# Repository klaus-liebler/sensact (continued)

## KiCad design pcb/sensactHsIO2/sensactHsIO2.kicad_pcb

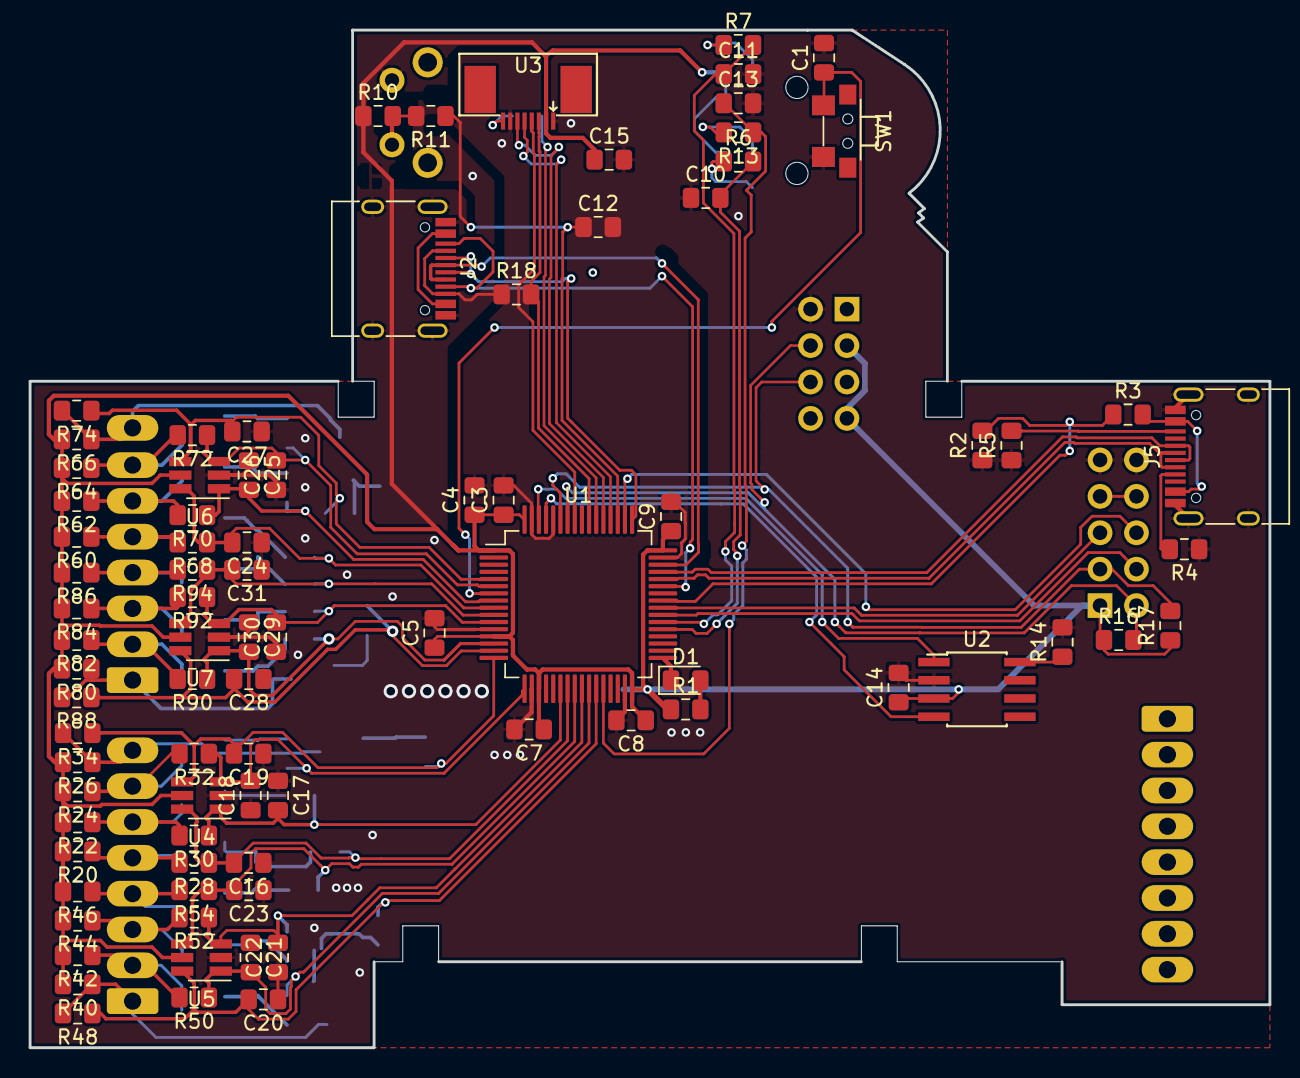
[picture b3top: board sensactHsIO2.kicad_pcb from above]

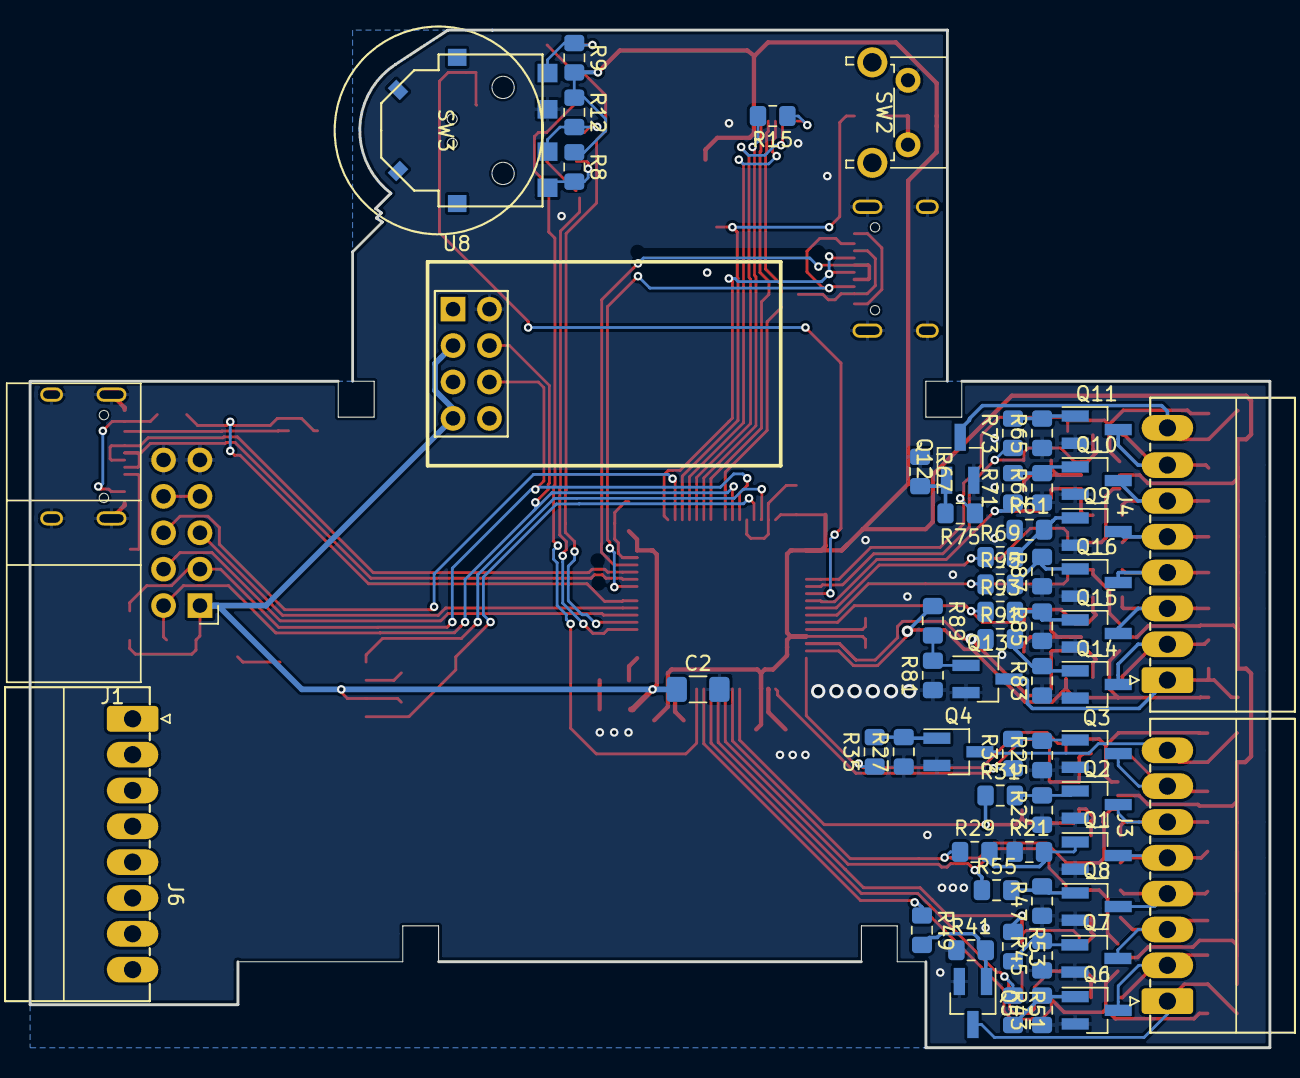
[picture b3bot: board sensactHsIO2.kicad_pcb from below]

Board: 2 copper layers, 86.5 x 71.0 mm, 146 parts (60 on the bottom side), 89 nets.

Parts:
C1, C3, C4, C5, C7, C8, C9, C10, C11, C12, C13, C14, C15, C16, C17, C18, C19, C20, C21, C22, C23, C24, C25, C26, C27, C28, C29, C30, C31: u1; C_0805_2012Metric_Pad1.15x1.40mm_HandSolder
C2: 4u7; C_1206_3216Metric_Pad1.42x1.75mm_HandSolder
D1: LED; LED_0805_2012Metric_Pad1.15x1.40mm_HandSolder
J1: SensactBus; IDC-Header_2x05_P2.54mm_Horizontal
J2, J5: USB_C_Receptacle_USB2.0; USB_C_Receptacle_HRO_TYPE-C-31-M-12
J3, J4, J6: Conn_01x08; PhoenixContact_MC_0,5_8-G-2.5_1x08_P2.50mm_Horizontal
Q1, Q2, Q3, Q4, Q5, Q6, Q7, Q8, Q9, Q10, Q11, Q12, Q13, Q14, Q15, Q16: Q_NMOS_GSD; SOT-23_Handsoldering
R1: K1; R_0805_2012Metric_Pad1.15x1.40mm_HandSolder
R2: 3k3; R_0805_2012Metric_Pad1.15x1.40mm_HandSolder
R3: 2k2; R_0805_2012Metric_Pad1.15x1.40mm_HandSolder
R4, R5: 5k1; R_0805_2012Metric_Pad1.15x1.40mm_HandSolder
R6, R7, R8, R9, R10, R11, R12, R13, R16, R17, R29, R31, R33, R35, R49, R51, R53, R55, R69, R71, R73, R75, R89, R91, R93, R95: 1k; R_0805_2012Metric_Pad1.15x1.40mm_HandSolder
R14, R20, R21, R22, R23, R24, R25, R26, R27, R28, R30, R32, R34, R40, R41, R42, R43, R44, R45, R46, R47, R48, R50, R52, R54, R60, R61, R62, R63, R64, R65, R66, R67, R68, R70, R72, R74, R80, R81, R82, R83, R84, R85, R86, R87, R88, R90, R92, R94: 10k; R_0805_2012Metric_Pad1.15x1.40mm_HandSolder
R15: 10R; R_0805_2012Metric_Pad1.15x1.40mm_HandSolder
R18: 22R; R_0805_2012Metric_Pad1.15x1.40mm_HandSolder
SW1: Reset; SW_SPST_2x4x3,5
SW2: SW_Push; SW_Tactile_SPST_Angled_PTS645Vx83-2LFS
SW3: Mitsumi_SIQ-02FVS3
U1: STM32F103R8Tx; LQFP-64_10x10mm_P0.5mm_handsolder
U2: SN65HVD230; SOIC-8_3.9x4.9mm_Pitch1.27mm_handsolder
U3: FP-096H09A; FPC_TOP_1x08-1MP_P0.50mm_Horizontal
U4, U5, U6, U7: SRV05-4; SOT-23-6_Handsoldering
U8: ESP-01v090; ESP-01

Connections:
+3V3: C2.1, C3.1, C4.1, C5.1, C7.1, C8.1, C9.1, C14.1, C15.1, J1.1, R1.1, R8.1, R9.2, R10.1, R12.1, R16.1, R17.1, R20.2, R22.2, R24.2, R26.2, R40.2, R42.2, R44.2, R46.2, R60.2, R62.2, R64.2, R66.2, R80.2, R82.2, R84.2, R86.2, U1.1, U1.13, U1.19, U1.32, U1.48, U1.64, U2.3, U3.2, U4.5, U5.5, U6.5, U7.5, U8.3, U8.7
+24V: J1.7, J1.8
/INT0: J1.4, U1.39
/INT1: J1.5, U1.40
/INT2: J1.6, U1.50
/NRST: C1.1, SW1.1, U1.7
/RX: J2.A8, J2.B8, U1.43
/SWCLK: J2.A7, J2.B7, U1.49
/SWDIO: J2.A6, J2.B6, U1.46
/USB+: J5.A6, J5.B6, U1.45
/USB-: J5.A7, J5.B7, U1.44
/io4_0/OUT0: J3.1, Q5.3, R40.1, R48.2
/io4_0/OUT1: J3.2, Q6.3, R42.1, R50.2
/io4_0/OUT2: J3.3, Q7.3, R44.1, R52.2
/io4_0/OUT3: J3.4, Q8.3, R46.1, R54.2
/io4_1/OUT0: J3.5, Q1.3, R20.1, R28.2
/io4_1/OUT1: J3.6, Q2.3, R22.1, R30.2
/io4_1/OUT2: J3.7, Q3.3, R24.1, R32.2
/io4_1/OUT3: J3.8, Q4.3, R26.1, R34.2
/io4_2/OUT0: J4.1, Q13.3, R80.1, R88.2
/io4_2/OUT1: J4.2, Q14.3, R82.1, R90.2
/io4_2/OUT2: J4.3, Q15.3, R84.1, R92.2
/io4_2/OUT3: J4.4, Q16.3, R86.1, R94.2
/io4_3/OUT0: J4.5, Q9.3, R60.1, R68.2
/io4_3/OUT1: J4.6, Q10.3, R62.1, R70.2
/io4_3/OUT2: J4.7, Q11.3, R64.1, R72.2
/io4_3/OUT3: J4.8, Q12.3, R66.1, R74.2
CAN_RX: U1.61, U2.4
CAN_TX: U1.62, U2.1
DAC0: J6.1, U1.20
DAC1: J6.2, U1.21
GND: C1.2, C2.2, C3.2, C4.2, C5.2, C7.2, C8.2, C9.2, C10.1, C11.2, C12.2, C13.2, C14.2, C15.2, C16.1, C17.1, C18.1, C19.1, C20.1, C21.1, C22.1, C23.1, C24.1, C25.1, C26.1, C27.1, C28.1, C29.1, C30.1, C31.1, J1.9, J1.10, J2.A1, J2.A12, J2.B1, J2.B12, J2.S1, J5.A1, J5.A12, J5.B1, J5.B12, J5.S1, Q1.2, Q2.2, Q3.2, Q4.2, Q5.2, Q6.2, Q7.2, Q8.2, Q9.2, Q10.2, Q11.2, Q12.2, Q13.2, Q14.2, Q15.2, Q16.2, R2.1, R4.1, R5.1, R14.2, R21.1, R23.1, R25.1, R27.1, R41.1, R43.1, R45.1, R47.1, R61.1, R63.1, R65.1, R67.1, R81.1, R83.1, R85.1, R87.1, SW1.2, SW2.1, SW3.C, U1.12, U1.18, U1.31, U1.47, U1.60, U1.63, U2.2, U3.1, U3.7, U4.2, U5.2, U6.2, U7.2, U8.2
I00: C20.2, R48.1, R49.1, U1.27, U5.6
I01: C21.2, R50.1, R51.1, U1.26, U5.1
I02: C22.2, R52.1, R53.1, U1.25, U5.3
I03: C23.2, R54.1, R55.1, U1.24, U5.4
I04: C16.2, R28.1, R29.1, U1.23, U4.6
I05: C17.2, R30.1, R31.1, U1.22, U4.1
I06: C18.2, R32.1, R33.1, U1.17, U4.3
I07: C19.2, R34.1, R35.1, U1.16, U4.4
I08: C28.2, R88.1, R89.1, U1.15, U7.6
I09: C29.2, R90.1, R91.1, U1.14, U7.1
I10: C30.2, R92.1, R93.1, U1.11, U7.3
I11: C31.2, R94.1, R95.1, U1.10, U7.4
I12: C24.2, R68.1, R69.1, U1.9, U6.6
I13: C25.2, R70.1, R71.1, U1.8, U6.1
I14: C26.2, R72.1, R73.1, U1.6, U6.3
I15: C27.2, R74.1, R75.1, U1.5, U6.4
LCD_BL: R15.2, U1.54
LCD_CLK: R18.2, U1.55, U3.3
LCD_MOSI: U1.57, U3.4
LCD_RS: U1.52, U3.5
LCD_RST: U1.53, U3.6
LED: D1.1, U1.33
unnamed: D1.2, R1.2
unnamed: J2.A4, J2.A9, J2.B4, J2.B9
unnamed: J5.A4, J5.A9, J5.B4, J5.B9, R3.2
unnamed: J5.A5, R4.2
unnamed: J5.B5, R5.2
unnamed: Q1.1, R21.2, R29.2
unnamed: Q2.1, R23.2, R31.2
unnamed: Q3.1, R25.2, R33.2
unnamed: Q4.1, R27.2, R35.2
unnamed: Q5.1, R41.2, R49.2
unnamed: Q6.1, R43.2, R51.2
unnamed: Q7.1, R45.2, R53.2
unnamed: Q8.1, R47.2, R55.2
unnamed: Q9.1, R61.2, R69.2
unnamed: Q10.1, R63.2, R71.2
unnamed: Q11.1, R65.2, R73.2
unnamed: Q12.1, R67.2, R75.2
unnamed: Q13.1, R81.2, R89.2
unnamed: Q14.1, R83.2, R91.2
unnamed: Q15.1, R85.2, R93.2
unnamed: Q16.1, R87.2, R95.2
unnamed: R6.1, R8.2, SW3.A
unnamed: R7.1, R9.1, SW3.B
unnamed: R10.2, R11.2, SW2.2
unnamed: R12.2, R13.2, SW3.S
unnamed: R14.1, U2.8
unnamed: R15.1, U3.8
ROTA: C10.2, R6.2, U1.37
ROTB: C11.1, R7.2, U1.38
ROTS: C13.1, R13.1, U1.28
S: C12.1, R11.1, U1.51
SCL1: J1.2, R16.2, U1.58, U8.4
SDA1: J1.3, R17.2, U1.59, U8.6
SWO: J2.A5, J2.B5, R18.1
VBUS: R2.2, R3.1, U1.41

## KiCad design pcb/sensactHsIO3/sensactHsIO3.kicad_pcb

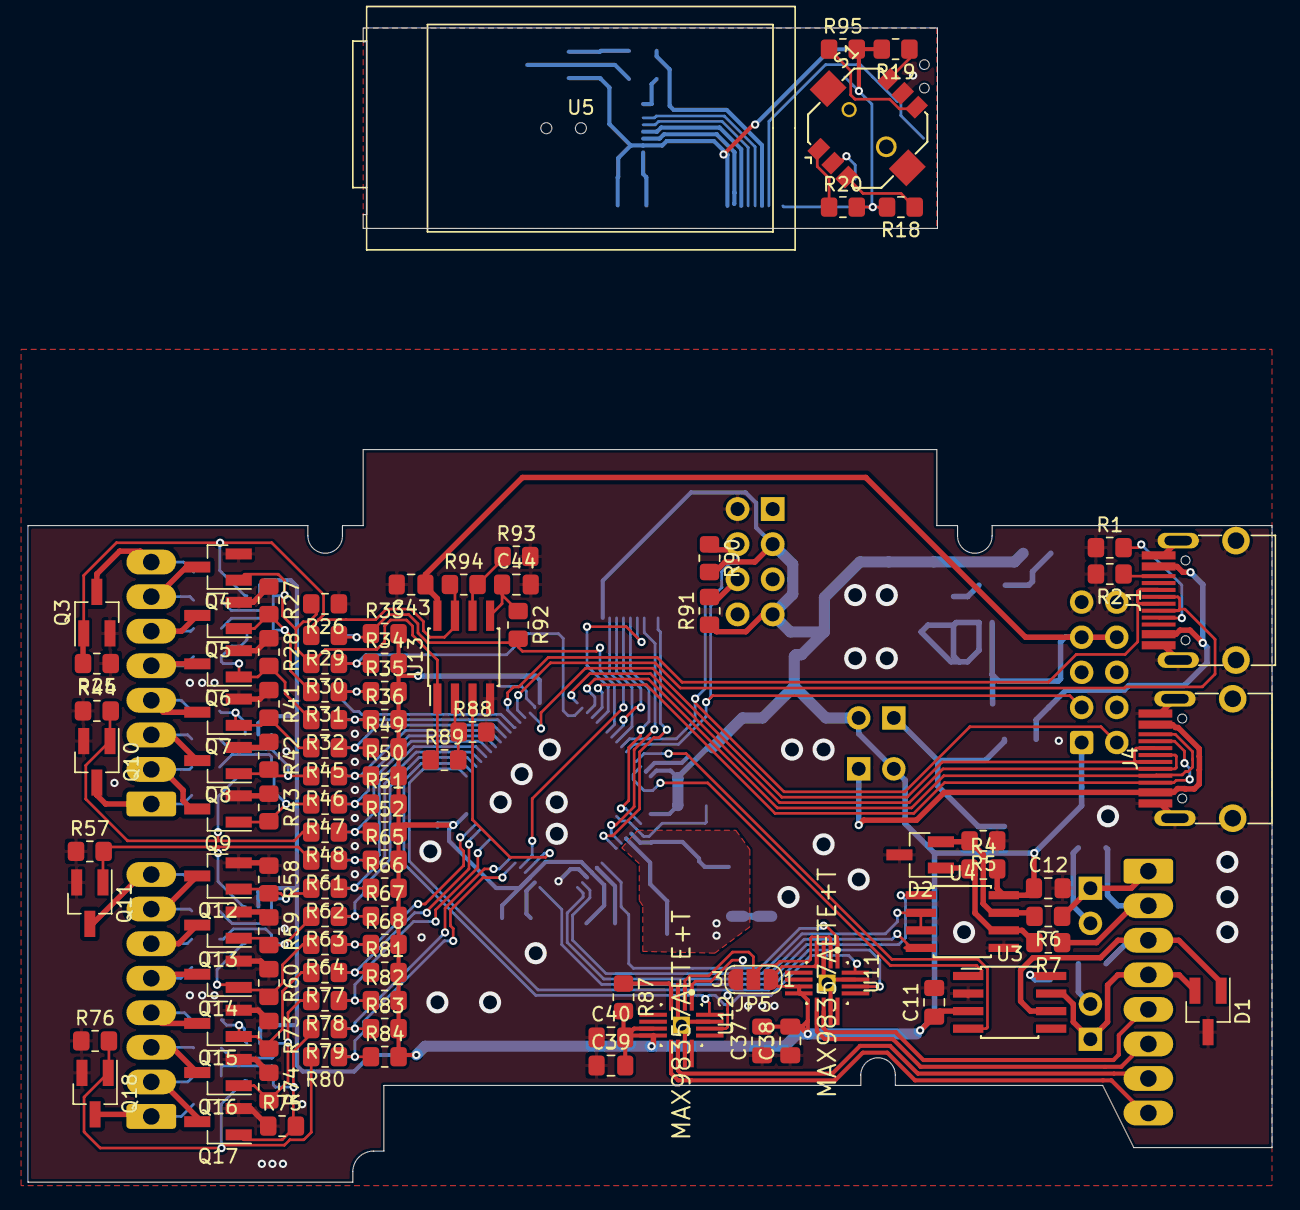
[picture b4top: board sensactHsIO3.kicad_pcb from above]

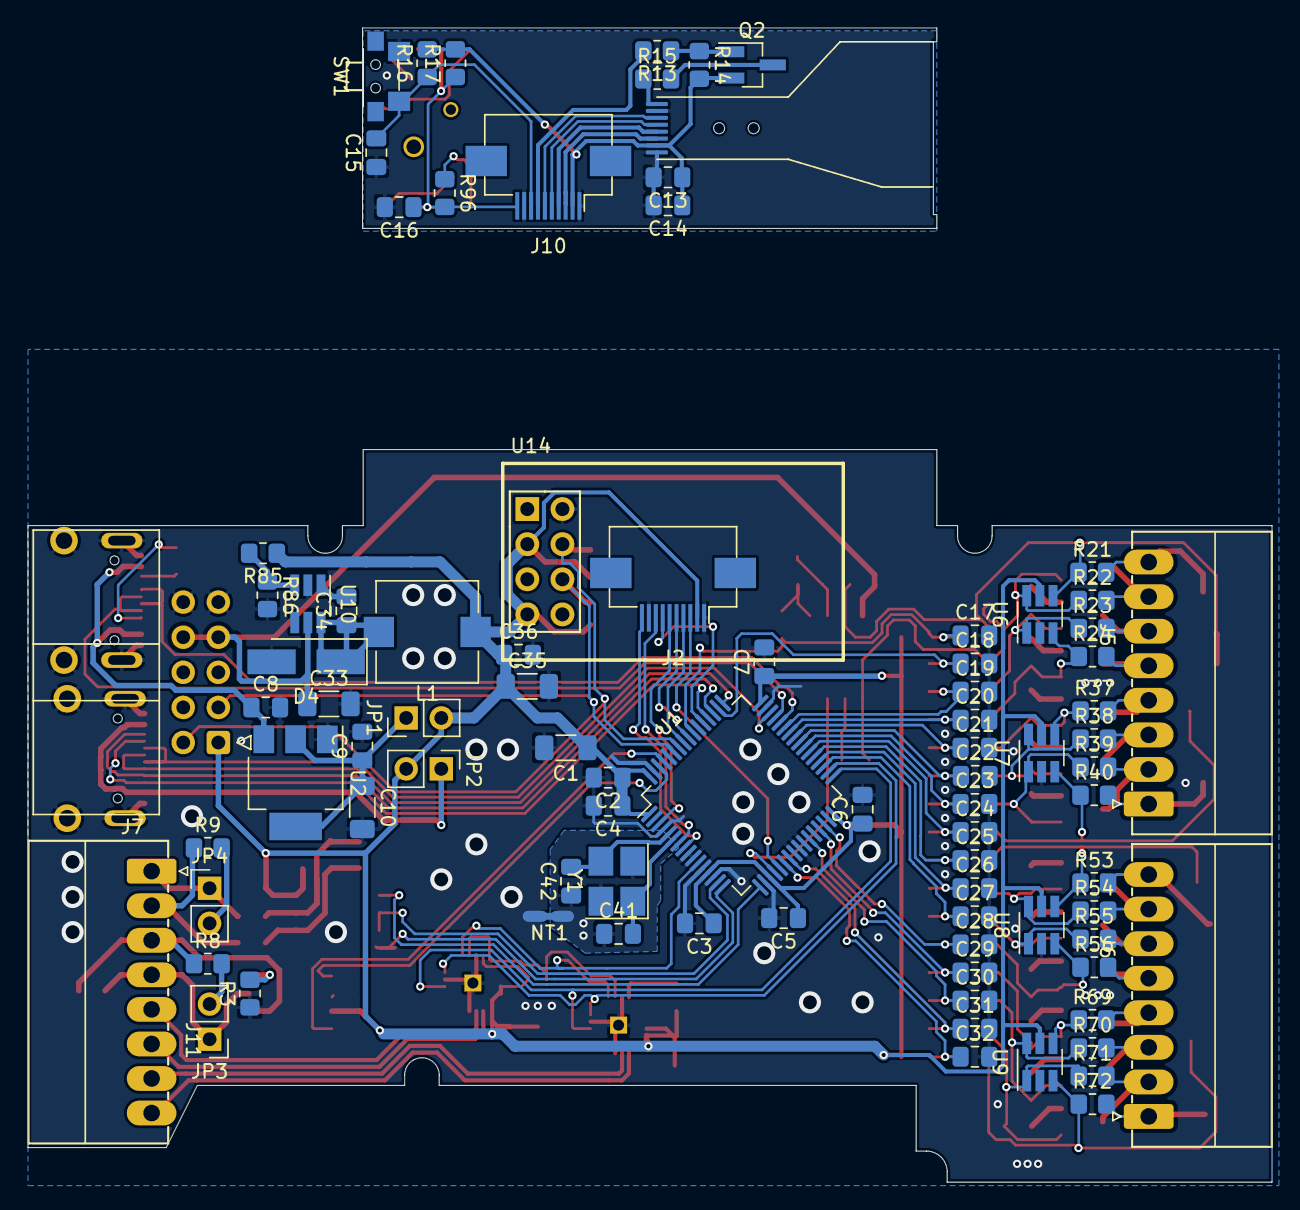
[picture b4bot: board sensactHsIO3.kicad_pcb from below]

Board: 2 copper layers, 90.0 x 53.0 mm, 189 parts (87 on the bottom side), 121 nets.

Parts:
C1, C33: 4u7; C_1206_3216Metric_Pad1.33x1.80mm_HandSolder
C2, C3, C4, C5, C6, C7, C9, C11, C12, C13, C15, C16, C17, C18, C19, C20, C21, C22, C23, C24, C25, C26, C27, C28, C29, C30, C31, C32, C34, C36, C38, C40, C43, C44: u1; C_0805_2012Metric_Pad1.18x1.45mm_HandSolder
C8: 1u; C_0805_2012Metric_Pad1.18x1.45mm_HandSolder
C10: 22u; C_1206_3216Metric_Pad1.33x1.80mm_HandSolder
C14: 2u2; C_0805_2012Metric_Pad1.18x1.45mm_HandSolder
C35: m1; C_1206_3216Metric_Pad1.33x1.80mm_HandSolder
C37, C39: 10u; C_0805_2012Metric_Pad1.18x1.45mm_HandSolder
C41, C42: 22p; C_0805_2012Metric_Pad1.18x1.45mm_HandSolder
D1: Nup2105l; SOT-23_Handsoldering
D2: SM712_SOT23; SOT-23_Handsoldering
D4: MBR0540; D_SMA_Handsoldering
J1: USB; USB_C_Receptacle_HANDSOLDER
J2, J10: Conn_01x10; FFC_FPC_10_P0.50mm_Horizontal
J4: DEBUG; USB_C_Receptacle_HANDSOLDER
J5, J6, J11: Conn_01x08; PhoenixContact_MC_0,5_8-G-2.5_1x08_P2.50mm_Horizontal
J7: SensactBusConnector; IDC-Header_2x05_P2.54mm_Horizontal
JP1: USB_PSU; PinHeader_1x02_P2.54mm_Vertical
JP2: DEBUG_PSU; PinHeader_1x02_P2.54mm_Vertical
JP3: CAN_TERM; PinHeader_1x02_P2.54mm_Vertical
JP4: RS485_TERM; PinHeader_1x02_P2.54mm_Vertical
JP5: 12/9/6dB; SolderJumper-3_P1.3mm_Open_RoundedPad1.0x1.5mm_NumberLabels
L1: 33u; L_7.3x7.3_H4.5_handsolder
NT1: Net-Tie_2; NetTie-2_SMD_Pad0.5mm
Q2: IRLML5203; SOT-23_Handsoldering
Q3, Q4, Q5, Q6, Q7, Q8, Q9, Q10, Q11, Q12, Q13, Q14, Q15, Q16, Q17, Q18: IRLML6344; SOT-23_Handsoldering
R1, R2: 5k1; R_0805_2012Metric_Pad1.20x1.40mm_HandSolder
R3, R14, R25, R26, R27, R28, R33, R34, R35, R36, R41, R42, R43, R44, R49, R50, R51, R52, R57, R58, R59, R60, R65, R66, R67, R68, R73, R74, R75, R76, R81, R82, R83, R84, R88, R92, R93, R95: 10k; R_0805_2012Metric_Pad1.20x1.40mm_HandSolder
R4, R5: 20k; R_0805_2012Metric_Pad1.20x1.40mm_HandSolder
R6, R7: R; R_0805_2012Metric_Pad1.20x1.40mm_HandSolder
R8, R9: 120R; R_0805_2012Metric_Pad1.20x1.40mm_HandSolder
R13, R16, R20, R29, R30, R31, R32, R45, R46, R47, R48, R61, R62, R63, R64, R77, R78, R79, R80, R86: 1k; R_0805_2012Metric_Pad1.20x1.40mm_HandSolder
R15: 100R; R_0805_2012Metric_Pad1.20x1.40mm_HandSolder
R17, R89, R94, R96: 22k; R_0805_2012Metric_Pad1.20x1.40mm_HandSolder
R18, R90, R91: 4k7; R_0805_2012Metric_Pad1.20x1.40mm_HandSolder
R19: 2k2; R_0805_2012Metric_Pad1.20x1.40mm_HandSolder
R21, R22, R23, R24, R37, R38, R39, R40, R53, R54, R55, R56, R69, R70, R71, R72: 10R; R_0805_2012Metric_Pad1.20x1.40mm_HandSolder
R85: 3k3; R_0805_2012Metric_Pad1.20x1.40mm_HandSolder
R87: 220k; R_0805_2012Metric_Pad1.20x1.40mm_HandSolder
S1: ALPS_SKRHABE010; Alps_SKRHABE010
SW1: SW_Push; SW_SPST_2x4x3,5
U1: STM32F072RBTx; LQFP-64_10x10mm_P0.5mm
U2: AMS1117-3.3; SOT-223-3_TabPin2
U3: SN65HVD230; SOIC-8_3.9x4.9mm_Pitch1.27mm_handsolder
U4: MAX3485; SOIC-8_3.9x4.9mm_Pitch1.27mm_handsolder
U5: FP-114H03A
U6, U7, U8, U9: SRV05-4; SOT-23-6_Handsoldering
U10: LMR14206; SOT-23-6_Handsoldering
U11, U12: MAX98357AETE+T; MAX98357AETE
U13: LM358; SOIC-8_3.9x4.9mm_Pitch1.27mm_handsolder
U14: ESP-01v090; ESP-01
Y1: Crystal_GND24; Crystal_SMD_3225-4Pin_3.2x2.5mm_HandSoldering

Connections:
+3.3VP: C13.1, C14.1, J10.2, Q2.2, R14.2, R16.2, R17.2, U5.7
+3V3: C1.1, C2.1, C3.1, C4.1, C5.1, C6.1, C7.1, C11.1, C12.1, C35.1, C36.1, C37.2, C38.2, C39.2, C40.2, J2.2, J7.1, JP1.2, JP2.2, JP5.1, L1.1, R4.2, R33.2, R34.2, R35.2, R36.2, R49.2, R50.2, R51.2, R52.2, R65.2, R66.2, R67.2, R68.2, R81.2, R82.2, R83.2, R84.2, R85.1, R87.2, R90.2, R91.1, U1.1, U1.13, U1.19, U1.32, U1.48, U1.64, U3.3, U4.8, U6.5, U7.5, U8.5, U9.5, U11.4, U11.7, U11.8, U12.7, U12.8, U14.3, U14.7
+24V: C33.1, C43.1, J7.7, J7.8, U10.5, U13.8
/io4_A/OUT0: J5.8, Q3.3, R21.2
/io4_A/OUT1: J5.7, Q4.3, R22.2
/io4_A/OUT2: J5.6, Q5.3, R23.2
/io4_A/OUT3: J5.5, Q6.3, R24.2
/io4_B/OUT0: J5.4, Q7.3, R37.2
/io4_B/OUT1: J5.3, Q8.3, R38.2
/io4_B/OUT2: J5.2, Q9.3, R39.2
/io4_B/OUT3: J5.1, Q10.3, R40.2
/io4_B/S0: Q7.1, R37.1, R41.2, R45.2, U7.4
/io4_B/S1: Q8.1, R38.1, R42.2, R46.2, U7.6
/io4_C/OUT0: J6.8, Q11.3, R53.2
/io4_C/OUT1: J6.7, Q12.3, R54.2
/io4_C/OUT2: J6.6, Q13.3, R55.2
/io4_C/OUT3: J6.5, Q14.3, R56.2
/io4_C/S0: Q11.1, R53.1, R57.2, R61.2, U8.4
/io4_C/S1: Q12.1, R54.1, R58.2, R62.2, U8.6
/io4_D/OUT0: J6.4, Q15.3, R69.2
/io4_D/OUT1: J6.3, Q16.3, R70.2
/io4_D/OUT2: J6.2, Q17.3, R71.2
/io4_D/OUT3: J6.1, Q18.3, R72.2
/io4_D/S0: Q15.1, R69.1, R73.2, R77.2, U9.4
/io4_D/S1: Q16.1, R70.1, R74.2, R78.2, U9.6
/psu/CB: C34.2, U10.1
/psu/FB: R85.2, R86.1, U10.3
/psu/SW: C34.1, D4.1, L1.2, U10.6
AUDIO_L_N: J11.5, U11.10
AUDIO_L_P: J11.6, U11.9
AUDIO_R_N: J11.7, U12.10
AUDIO_R_P: J11.8, U12.9
CAN_H: D1.2, J11.4, JP3.1, U3.7
CAN_L: D1.1, J11.3, R8.1, U3.6
CAN_RX: U1.61, U3.4
CAN_TX: U1.62, U3.1
DAC1: U1.20, U13.3
DEBUG_RX: J4.A8, J4.B8, U1.52
DEBUG_TX: J4.A5, J4.B5, U1.51
GND: C1.2, C2.2, C3.2, C4.2, C5.2, C6.2, C7.2, C8.2, C9.2, C10.2, C11.2, C12.2, C17.2, C18.2, C19.2, C20.2, C21.2, C22.2, C23.2, C24.2, C25.2, C26.2, C27.2, C28.2, C29.2, C30.2, C31.2, C32.2, C33.2, C35.2, C36.2, C37.1, C38.1, C39.1, C40.1, C43.2, C44.2, D1.3, D2.3, D4.2, J1.A1, J1.A12, J1.B1, J1.B12, J1.S1, J2.1, J2.9, J4.A1, J4.A12, J4.B1, J4.B12, J4.S1, J7.9, J7.10, JP5.3, NT1.2, Q3.2, Q4.2, Q5.2, Q6.2, Q7.2, Q8.2, Q9.2, Q10.2, Q11.2, Q12.2, Q13.2, Q14.2, Q15.2, Q16.2, Q17.2, Q18.2, R1.1, R2.2, R3.1, R5.1, R25.1, R26.1, R27.1, R28.1, R41.1, R42.1, R43.1, R44.1, R57.1, R58.1, R59.1, R60.1, R73.1, R74.1, R75.1, R76.1, R86.2, R88.2, R93.2, U1.4, U1.9, U1.10, U1.12, U1.14, U1.18, U1.24, U1.25, U1.26, U1.31, U1.47, U1.63, U2.1, U3.2, U4.5, U6.2, U7.2, U8.2, U9.2, U10.2, U11.3, U11.11, U11.15, U11.17, U12.3, U12.11, U12.15, U12.17, U13.4, U14.2
GND1: C13.2, C14.2, C15.1, C16.2, J10.1, J10.9, S1.5, SW1.2, U5.2, U5.8
GNDA: C41.1, C42.1, NT1.1, Y1.2, Y1.4
HMI_BL_LCD: J10.7, R13.2
HMI_BL_LCDx: J2.7, U1.53
HMI_RESET_LCD: J10.6, U5.3
HMI_RESET_LCDx: J2.6, U1.3
HMI_RESET_SW: C15.2, J10.8, R16.1, SW1.1
HMI_RESET_SWx: J2.8, U1.7
HMI_RS_LCD: J10.5, U5.4
HMI_RS_LCDx: J2.5, U1.56
HMI_SCL_LCD: J10.3, U5.6
HMI_SCL_LCDx: J2.3, U1.21
HMI_SDA_LCD: J10.4, U5.5
HMI_SDA_LCDx: J2.4, U1.57
HMI_SW: C16.1, J10.10, R17.1, R18.2, R19.2, R20.2, R95.2, R96.2
HMI_SWx: J2.10, U1.8
I2S_CK: U1.34, U11.16, U12.16
I2S_SD: U1.11, U11.1, U12.1
I2S_WS: U1.33, U11.14, U12.14
IO0: C17.1, R29.1, R33.1, R92.2, U1.55
IO1: C18.1, R30.1, R34.1, U1.50
IO2: C19.1, R31.1, R35.1, U1.43
IO3: C20.1, R32.1, R36.1, U1.42
IO4: C21.1, R45.1, R49.1, U1.41
IO5: C22.1, R46.1, R50.1, U1.40
IO6: C23.1, R47.1, R51.1, U1.39
IO7: C24.1, R48.1, R52.1, U1.38
IO8: C25.1, R61.1, R65.1, U1.37
IO9: C26.1, R62.1, R66.1, U1.36
IO10: C27.1, R63.1, R67.1, U1.35
IO11: C28.1, R64.1, R68.1, U1.30
IO12: C29.1, R77.1, R81.1, U1.29
IO13: C30.1, R78.1, R82.1, U1.27
IO14: C31.1, R79.1, R83.1, U1.23
IO15: C32.1, R80.1, R84.1, U1.22
unnamed: C8.1, J1.A4, J1.A9, J1.B4, J1.B9, U2.3
unnamed: C41.2, U1.6, Y1.1
unnamed: C42.2, U1.5, Y1.3
unnamed: C44.1, R92.1, U13.5
unnamed: D2.1, R4.1, R7.2, U4.6
unnamed: D2.2, R5.2, R6.2, U4.7
unnamed: J1.A5, R1.2
unnamed: J1.B5, R2.1
unnamed: J4.A4, J4.A9, J4.B4, J4.B9, JP2.1
unnamed: JP3.2, R8.2
unnamed: JP4.2, R9.2
unnamed: JP5.2, U11.2, U12.2
unnamed: Q2.1, R13.1, R14.1
unnamed: Q2.3, R15.2
unnamed: Q5.1, R23.1, R27.2, R31.2, U6.1
unnamed: Q6.1, R24.1, R28.2, R32.2, U6.3
unnamed: Q9.1, R39.1, R43.2, R47.2, U7.1
unnamed: Q10.1, R40.1, R44.2, R48.2, U7.3
unnamed: Q13.1, R55.1, R59.2, R63.2, U8.1
unnamed: Q14.1, R56.1, R60.2, R64.2, U8.3
unnamed: Q17.1, R71.1, R75.2, R79.2, U9.1
unnamed: Q18.1, R72.1, R76.2, R80.2, U9.3
unnamed: R3.2, U3.8
unnamed: R15.1, U5.1
unnamed: R18.1, S1.3
unnamed: R19.1, S1.4
unnamed: R20.1, S1.1
unnamed: R87.1, U12.4
unnamed: R88.1, R89.2, U13.2
unnamed: R93.1, R94.2, U13.6
unnamed: R95.1, S1.6
unnamed: R96.1, S1.2
RS485_A: J11.2, R7.1, R9.1
RS485_B: J11.1, JP4.1, R6.1
RS485_DE: U1.15, U4.2, U4.3
RS485_RX: U1.17, U4.1
RS485_TX: U1.16, U4.4
S0: Q3.1, R21.1, R25.2, R29.2, R94.1, U6.4, U13.7
S1: Q4.1, R22.1, R26.2, R30.2, R89.1, U6.6, U13.1
SCL: J7.2, R90.1, U1.58, U14.4
SDA: J7.3, R91.2, U1.59, U14.6
SWCLK: J4.A7, J4.B7, U1.49
SWDIO: J4.A6, J4.B6, U1.46
USB_DM: J1.A6, J1.B6, U1.44
USB_DP: J1.A7, J1.B7, U1.45
USB_VBUS: C9.1, C10.1, JP1.1, U2.2
